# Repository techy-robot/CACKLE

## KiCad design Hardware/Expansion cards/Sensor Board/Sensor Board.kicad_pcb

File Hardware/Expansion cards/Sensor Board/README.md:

---
modified: 2025-01-12T19:10:57-07:00
---

# Sensor Board

This is a connector breakout board for vertical mezzanine connectors on a hub. It has one Qwiic connector, two nanoSPI connectors, and header breakouts for the free pins, chip select pins, and the SPI pins. Essentially it breaks out every pin accessible via the mezzanine connector.

Note that this does not fit the hubs by default because it sticks into the hub chaining headers. You will need a Vertical Spacer, or use the [2 connector sensor breakout](../2%20connector%20Sensor%20Board/README.md) instead, which does fit.

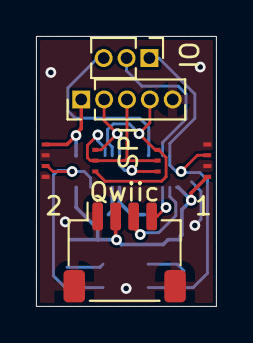
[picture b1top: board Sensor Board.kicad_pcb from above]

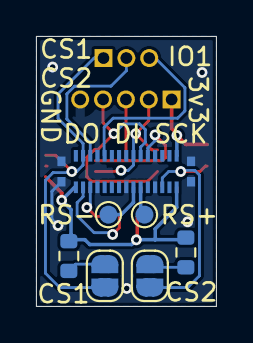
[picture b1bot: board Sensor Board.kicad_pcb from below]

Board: 2 copper layers, 10.0 x 15.0 mm, 12 parts (7 on the bottom side), 14 nets.

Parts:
J1: SPI; PinHeader_1x05_P1.27mm_Vertical
J2, J5: 7 pin FPC 0.3mm Panasonic Y3b; fpc_7pin_0.3mm_connector Panasonic
J3: free pins; PinHeader_1x03_P1.27mm_Vertical
J7: JST SH; JST_SH_SM04B-SRSS-TB_1x04-1MP_P1.00mm_Horizontal
J15: TE 3-2363962-0 Connector; TE_mezzanine_conn_3-2363962-0
JP1: CS2; SolderJumper-2_P1.3mm_Open_RoundedPad1.0x1.5mm
JP2: CS1; SolderJumper-2_P1.3mm_Open_RoundedPad1.0x1.5mm
R2, R4: 10k; R_0603_1608Metric
TP1: RS485-; TestPoint_Pad_D1.0mm
TP2: RS485+; TestPoint_Pad_D1.0mm

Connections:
CS1: J2.5, J3.1, J15.4, J15.27, JP2.1 (A)
CS2: J3.2, J5.5, J15.6, J15.25, JP1.1 (A)
Free1: J3.3, J15.10, J15.21
GND: J1.5, J2.3, J2.7, J5.3, J5.7, J7.1, J7.MP (MountPin), J15.7, J15.8, J15.15, J15.16, J15.23, J15.24, J15.MP (MountPin)
MISO1: J1.3, J2.4, J5.4, J15.9, J15.22
MOSI1: J1.4, J2.6, J5.6, J15.11, J15.20
unnamed: JP1.2 (B), R2.2
unnamed: JP2.2 (B), R4.2
RS485+: J15.12, J15.19, TP2.1
RS485-: J15.14, J15.17, TP1.1
SCK1: J1.2, J2.2, J5.2, J15.13, J15.18
SCL1: J7.4, J15.5, J15.26
SDA1: J7.3, J15.3, J15.28
VDD: J1.1, J2.1, J5.1, J7.2, J15.1, J15.2, J15.29, J15.30, R2.1, R4.1

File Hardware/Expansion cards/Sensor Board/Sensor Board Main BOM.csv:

"Id";"Designator";"Footprint";"Quantity";"Designation";"Supplier and ref";
1;"J1";"PinHeader_1x05_P1.27mm_Vertical";1;"SPI";;;
2;"J7";"JST_SH_SM04B-SRSS-TB_1x04-1MP_P1.00mm_Horizontal";1;"JST SH";;;
3;"J3";"PinHeader_1x03_P1.27mm_Vertical";1;"free pins";;;
4;"J2,J5";"fpc_7pin_0.3mm_connector Panasonic";2;"7 pin FPC 0.3mm Panasonic Y3b";;;
5;"R2,R4";"R_0603_1608Metric";2;"10k";;;
6;"J15";"TE_mezzanine_conn_3-2363962-0";1;"TE 3-2363962-0 Connector";;;

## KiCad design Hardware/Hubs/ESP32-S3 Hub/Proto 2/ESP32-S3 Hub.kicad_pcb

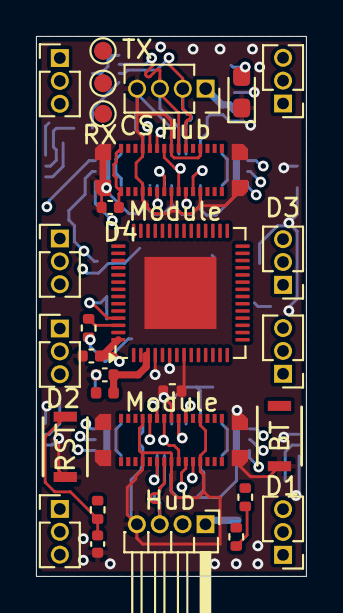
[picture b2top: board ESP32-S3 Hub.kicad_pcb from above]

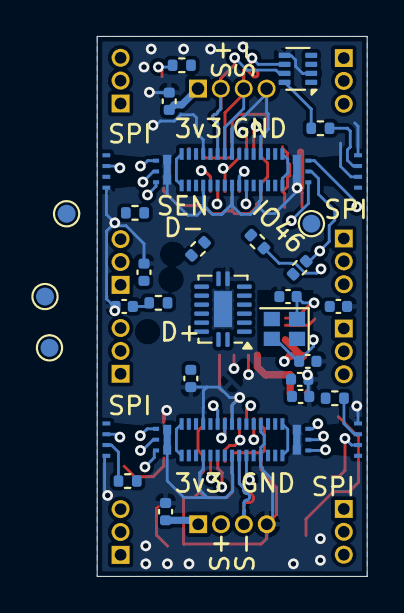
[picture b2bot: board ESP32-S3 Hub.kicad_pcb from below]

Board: 6 copper layers, 15.0 x 30.0 mm, 61 parts (32 on the bottom side), 59 nets.

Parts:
C1, C14: 22uF; C_0402_1005Metric
C2, C7, C9, C13: 1uF; C_0402_1005Metric
C3, C4, C5, C6, C8, C10: 0.1uF; C_0402_1005Metric
C11, C12: 12pF; C_0402_1005Metric
D1: 2.6~3.1 Fv Green 5ma; LED_0603_1608Metric_Pad1.05x0.95mm_HandSolder
FB1: 120ohm imp @100mhz, 1 amp; L_0402_1005Metric
J1, J2, J4, J6, J7, J9, J10, J12: 1.27mm 3pin socket; PinHeader_1x03_P1.27mm_Vertical
J3, J5, J8, J11: 7 pin FPC 0.3mm Panasonic Y3b; fpc_7pin_0.3mm_connector Panasonic
J13, J16: TE 3-2363961-0 receptacle; TE_mezzanine_rec_3-2363961-0
J14, J17: TE 3-2363962-0 Connector; TE_mezzanine_conn_3-2363962-0
J21: 1.27mm 4 pin socket; PinSocket_1x04_P1.27mm_Vertical
J22: 1.27mm 4 pin header; PinHeader_1x04_P1.27mm_Horizontal
R1: 100k; R_0402_1005Metric
R2, R7, R8, R9, R11, R18, R19, R20: 10k; R_0402_1005Metric
R3, R4, R5: 33ohm; R_0402_1005Metric
R6: 22 ohm; R_0402_1005Metric
R10: 80.6 ohm; R_0402_1005Metric
SW1, SW2: Mitsumi R-667996; R-667995_MIT
TP1: S-EN; TestPoint_Pad_D1.0mm
TP2: RX; TestPoint_Pad_D1.0mm
TP3: TX; TestPoint_Pad_D1.0mm
TP4: IO46; TestPoint_Pad_D1.0mm
TP12: SRCLK; TestPoint_Pad_D1.0mm
TP14: SER; TestPoint_Pad_D1.0mm
TP20: CS0; TestPoint_Pad_D1.0mm
U1: ESP32-S3; QFN-56-1EP_7x7mm_P0.4mm_EP4x4mm
U2: 74HC595; DHVQFN-16-1EP_2.5x3.5mm_P0.5mm_EP1x2mm
U3: THVD1420DRLR; SOT-583-8
Y1: ABM11-40.000MHZ-B1U-T3, 10ppm, 10pF; Crystal_SMD_2016-4Pin_2.0x1.6mm

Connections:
1A: J1.1, U1.15 (GPIO10)
1B: J1.2, U1.16 (GPIO11)
1C: J1.3, U1.17 (GPIO12)
1CSA-A: J2.1, U1.13 (GPIO8)
1CSA-B: J2.2, U1.14 (GPIO9)
2A: J4.1, U1.18 (GPIO13)
2B: J4.2, U1.19 (GPIO14)
2C: J4.3, U1.21 (XTAL_32K_P)
2CSA-A: J6.1, U1.11 (GPIO6)
2CSA-B: J6.2, U1.12 (GPIO7)
3A: J7.1, U1.22 (XTAL_32K_N)
3B: J7.2, U1.23 (GPIO17)
3C: J7.3, U1.36 (SPICLK_N)
3CSA-A: J9.1, U1.10 (GPIO5)
3CSA-B: J9.2, U1.9 (GPIO4)
4A: J10.1, U1.38 (GPIO33)
4B: J10.2, U1.39 (GPIO34)
4C: J10.3, U1.37 (SPICLK_P)
4CSA-A: J12.1, U1.6 (GPIO1)
4CSA-B: J12.2, U1.7 (GPIO2)
BOOT: SW1.2, U1.5 (GPIO0)
CS1: J3.5, R2.2, U2.15 (QA)
CS2: J5.5, R18.2, U2.1 (QB)
CS3: J8.5, R19.2, U2.2 (QC)
CS4: J11.5, R20.2, U2.3 (QD)
CS5: J13.3, J13.28, U2.4 (QE)
CS6: J13.5, J13.26, U2.5 (QF)
CS7: J16.3, J16.28, U2.6 (QG)
CS8: J16.5, J16.26, U2.7 (QH)
Free1: J13.9, J13.22, U1.40 (GPIO35)
Free2: J16.9, J16.22, U1.41 (GPIO36)
GND: C1.2, C2.2, C3.2, C4.2, C5.2, C6.1, C7.2, C8.2, C9.1, C10.2, C11.2, C12.2, C13.2, C14.2, D1.1 (K), J3.3, J3.7, J5.3, J5.7, J8.3, J8.7, J11.3, J11.7, J13.7, J13.8, J13.15, J13.16, J13.23, J13.24, J13.MP (MountPin), J14.7, J14.8, J14.15, J14.16, J14.23, J14.24, J14.MP (MountPin), J16.7, J16.8, J16.15, J16.16, J16.23, J16.24, J16.MP (MountPin), J17.7, J17.8, J17.15, J17.16, J17.23, J17.24, J17.MP (MountPin), J21.4, J22.4, R1.2, SW1.1, SW2.1, U1.57 (GND), U2.8 (GND), U2.17 (GND), U3.2 (~RE), U3.5 (GND), Y1.2, Y1.4
LED: R10.1, U1.51 (GPIO45)
MISO1: J3.4, J5.4, J8.4, J11.4, J13.10, J13.21, J16.10, J16.21, R5.2
MOSI1: J3.6, J5.6, J8.6, J11.6, J13.12, J13.19, J16.12, J16.19, R4.2
NRST: C13.1, R7.1, SW2.2, U1.4 (CHIP_PU)
unnamed: C4.1, FB1.1, U1.2 (VDD3P3), U1.3 (VDD3P3)
unnamed: C11.1, R6.1, Y1.3
unnamed: D1.2 (A), R10.2
unnamed: R1.1, U1.8 (GPIO3)
unnamed: TP4.1, U1.52 (GPIO46)
unnamed: R3.1, U1.44 (MTCK)
unnamed: R5.1, U1.47 (MTDI)
unnamed: R4.1, U1.45 (MTDO)
unnamed: C12.1, U1.53 (XTAL_N), Y1.1
unnamed: R6.2, U1.54 (XTAL_P)
RS485+: J13.11, J13.20, J14.12, J14.19, J16.11, J16.20, J17.12, J17.19, J21.2, J22.2, U3.7 (B)
RS485-: J13.13, J13.18, J14.14, J14.17, J16.13, J16.18, J17.14, J17.17, J21.3, J22.3, U3.6 (A)
SCK1: J3.2, J5.2, J8.2, J11.2, J13.14, J13.17, J16.14, J16.17, R3.2
SCL1: J13.6, J13.25, J14.5, J14.26, J16.6, J16.25, J17.5, J17.26, R9.2, U1.43 (GPIO38)
SDA1: J13.4, J13.27, J14.3, J14.28, J16.4, J16.27, J17.3, J17.28, R8.2, U1.42 (GPIO37)
ShiftCLK: TP12.1, U1.25 (GPIO19/USB_D-), U2.11 (SRCLK)
ShiftData: TP14.1, U1.26 (GPIO20/USB_D+), U2.14 (SER)
ShiftEn: R11.1, TP1.1, U1.27 (GPIO21), U2.13 (~OE)
ShiftRegCLK: U1.24 (GPIO18), U2.12 (RCLK)
UART0-RTS/CS0: TP20.1, U1.48 (MTMS), U3.3 (DE)
UART0_RX: TP2.1, U1.50 (U0RXD), U3.1 (RO)
UART0_TX: TP3.1, U1.49 (U0TXD), U3.4 (DI)
VDD: C1.1, C2.1, C3.1, C5.1, C6.2, C7.1, C8.1, C9.2, C10.1, C14.1, FB1.2, J3.1, J5.1, J8.1, J11.1, J13.1, J13.2, J13.29, J13.30, J14.1, J14.2, J14.29, J14.30, J16.1, J16.2, J16.29, J16.30, J17.1, J17.2, J17.29, J17.30, J21.1, J22.1, R2.1, R7.2, R8.1, R9.1, R11.2, R18.1, R19.1, R20.1, U1.20 (VDD3P3_RTC), U1.29 (VDD_SPI), U1.46 (VDD3P3_CPU), U1.55 (VDDA), U1.56 (VDDA), U2.16 (VCC), U3.8 (VCC)

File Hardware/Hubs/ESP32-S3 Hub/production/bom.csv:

Designator,Footprint,Quantity,Value,LCSC Part #
"C1, C14",0402,2,22uF,C415703
"C10, C3, C4, C5, C6, C8",0402,6,0.1uF,C1525
"C11, C12",0402,2,12pF,C1547
"C13, C2, C7, C9",0402,4,1uF,C52923
D1,0603,1,2.6~3.1 Fv Green 5ma,C3028858
FB1,0402,1,"120ohm imp @100mhz, 1 amp",C82861
"J13, J16",TE_mezzanine_rec_3-2363961-0,2,TE 3-2363961-0 receptacle,C425103
"J14, J17",TE_mezzanine_conn_3-2363962-0,2,TE 3-2363962-0 Connector,C425104
R1,0402,1,100k,C25741
R10,0402,1,80.6 ohm,C185392
"R11, R18, R19, R2, R20, R7, R8, R9",0402,8,10k,C25744
"R3, R4, R5",0402,3,33ohm,C25105
R6,0402,1,22 ohm,C25092
"SW1, SW2",R-667995_MIT,2,Mitsumi R-667996,C4365007
U1,QFN-56-1EP_7x7mm_P0.4mm_EP4x4mm,1,ESP32-S3,C3013940
U2,DHVQFN-16-1EP_2.5x3.5mm_P0.5mm_EP1x2mm,1,74HC595,C730243
Y1,Crystal_SMD_2016-4Pin_2.0x1.6mm,1,"ABM11-40.000MHZ-B1U-T3, 10ppm, 10pF",C648973

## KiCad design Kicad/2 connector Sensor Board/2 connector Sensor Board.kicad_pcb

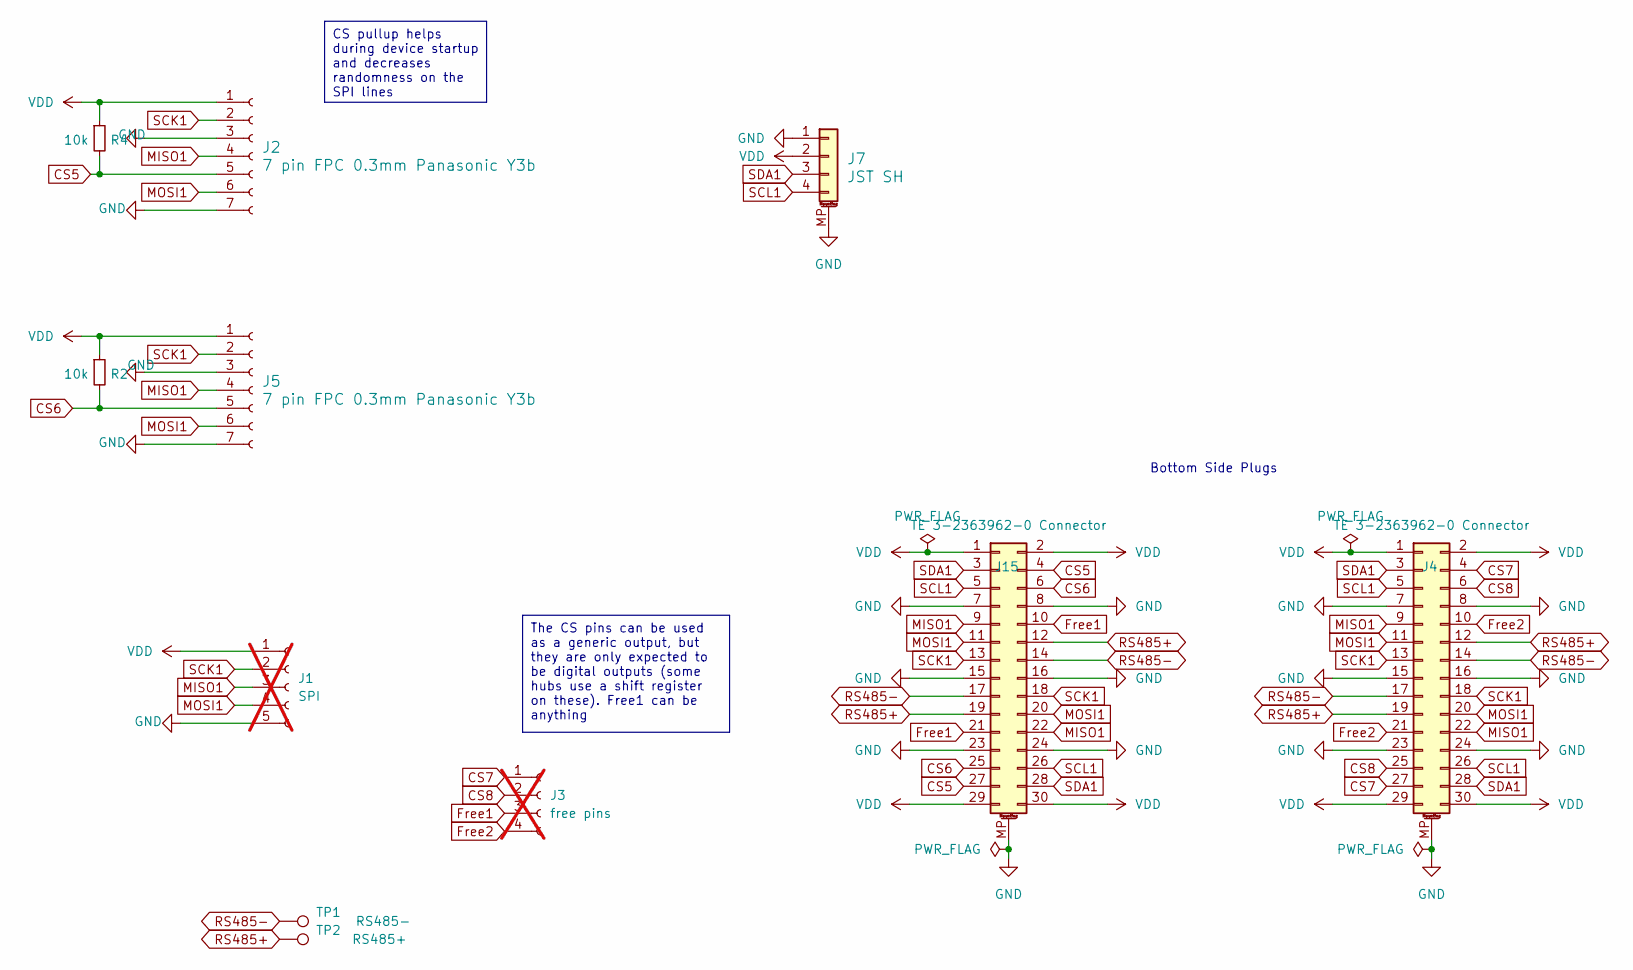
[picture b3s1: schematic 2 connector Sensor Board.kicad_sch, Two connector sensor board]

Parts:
J1: SPI; PinHeader_1x05_P1.27mm_Vertical; not fitted
J2, J5: 7 pin FPC 0.3mm Panasonic Y3b; fpc_7pin_0.3mm_connector Panasonic
J3: free pins; PinHeader_1x04_P1.27mm_Vertical; not fitted
J4, J15: TE 3-2363962-0 Connector; TE_mezzanine_conn_3-2363962-0
J7: JST SH; JST_SH_SM04B-SRSS-TB_1x04-1MP_P1.00mm_Horizontal
R2, R4: 10k; R_0402_1005Metric
TP1: RS485-; TestPoint_Pad_D1.0mm
TP2: RS485+; TestPoint_Pad_D1.0mm

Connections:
CS1: J2.5, J15.4, J15.27, R4.2
CS2: J5.5, J15.6, J15.25, R2.2
CS3: J3.1, J4.4, J4.27
CS4: J3.2, J4.6, J4.25
Free1: J3.3, J15.10, J15.21
Free2: J3.4, J4.10, J4.21
GND: J1.5, J2.3, J2.7, J4.7, J4.8, J4.15, J4.16, J4.23, J4.24, J4.MP (MountPin), J5.3, J5.7, J7.1, J7.MP (MountPin), J15.7, J15.8, J15.15, J15.16, J15.23, J15.24, J15.MP (MountPin)
MISO1: J1.3, J2.4, J4.9, J4.22, J5.4, J15.9, J15.22
MOSI1: J1.4, J2.6, J4.11, J4.20, J5.6, J15.11, J15.20
RS485+: J4.12, J4.19, J15.12, J15.19, TP2.1
RS485-: J4.14, J4.17, J15.14, J15.17, TP1.1
SCK1: J1.2, J2.2, J4.13, J4.18, J5.2, J15.13, J15.18
SCL1: J4.5, J4.26, J7.4, J15.5, J15.26
SDA1: J4.3, J4.28, J7.3, J15.3, J15.28
VDD: J1.1, J2.1, J4.1, J4.2, J4.29, J4.30, J5.1, J7.2, J15.1, J15.2, J15.29, J15.30, R2.1, R4.1

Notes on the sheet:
CS pullup helps during device startup and decreases randomness on the SPI lines
The CS pins can be used as a generic output, but they are only expected to be digital outputs (some hubs use a shift register on these). Free1 can be anything
Bottom Side Plugs

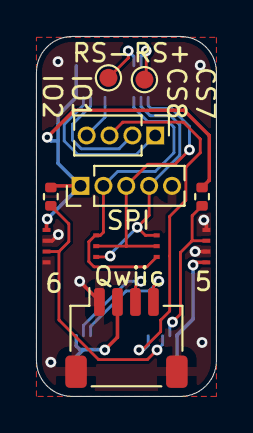
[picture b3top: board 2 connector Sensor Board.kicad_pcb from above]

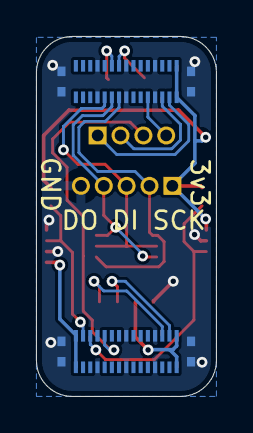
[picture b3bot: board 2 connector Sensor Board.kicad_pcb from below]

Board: 2 copper layers, 10.0 x 20.0 mm, 11 parts (2 on the bottom side), 15 nets.

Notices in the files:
Hardware/Hubs/ESP32-S3 Hub/Proto 2/ESP32-S3 Hub.kicad_pcb:
Licensed under CERN-OHL-S v2
